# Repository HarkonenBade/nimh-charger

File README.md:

# nimh-charger
Ni-MH and Ni-Cd battery trickle charger

Based on the schematic and design of Big Clive https://www.youtube.com/watch?v=wVnAH17f4jg with my own improvements to the PCB design for two layer manufacture.

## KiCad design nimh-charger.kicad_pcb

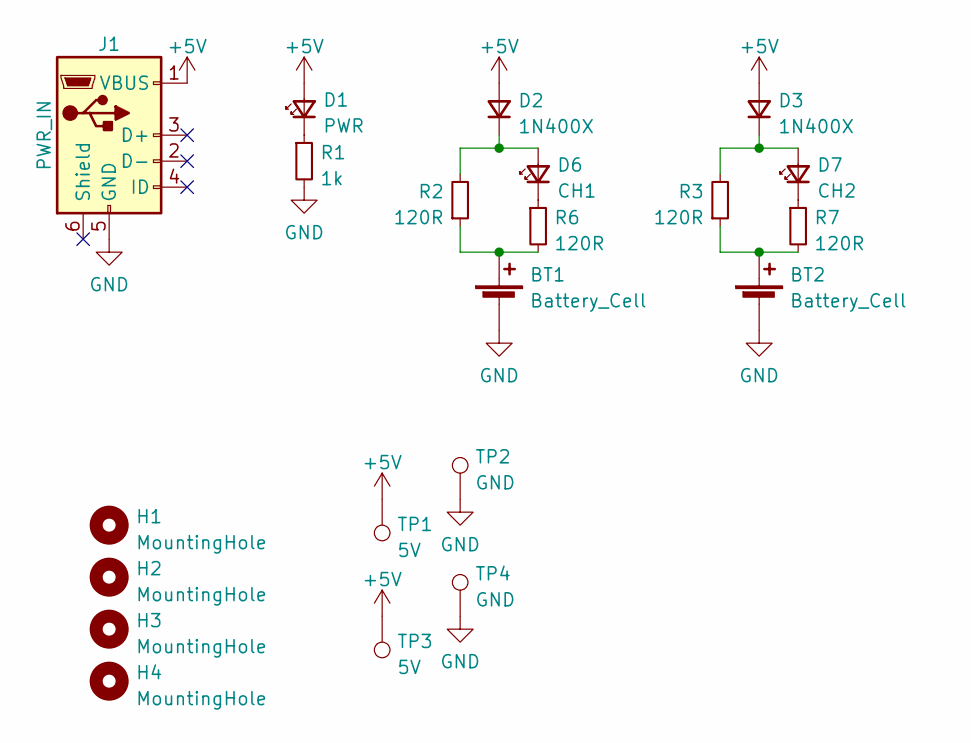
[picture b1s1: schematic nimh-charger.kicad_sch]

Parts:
BT1, BT2: Battery_Cell; BatteryHolder_Keystone_2460_1xAA
D1: PWR; LED_0805_2012Metric; LCSC C965812
D2, D3: 1N400X; D_SMA; LCSC C2892325
D6: CH1; LED_0805_2012Metric; LCSC C965812
D7: CH2; LED_0805_2012Metric; LCSC C965812
H1, H2, H3, H4: MountingHole; MountingHole_3.2mm_M3_DIN965
J1: PWR_IN; USB_Micro-B_Molex-105017-0001; LCSC C136000
R1: 1k; R_0805_2012Metric
R2, R3, R6, R7: 120R; R_0805_2012Metric
TP1, TP3: 5V; TestPoint_Pad_2.5x2.5mm
TP2, TP4: GND; TestPoint_Pad_2.5x2.5mm

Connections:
+5V: D1.2 (A), D2.2 (A), D3.2 (A), J1.1 (VBUS), TP1.1, TP3.1
GND: BT1.2 (-), BT2.2 (-), J1.5 (GND), R1.2, TP2.1, TP4.1
unnamed: BT1.1 (+), R2.1, R6.2
unnamed: D1.1 (K), R1.1
unnamed: D2.1 (K), D6.2 (A), R2.2
unnamed: D3.1 (K), D7.2 (A), R3.2
unnamed: D6.1 (K), R6.1
unnamed: D7.1 (K), R7.1
unnamed: BT2.1 (+), R3.1, R7.2

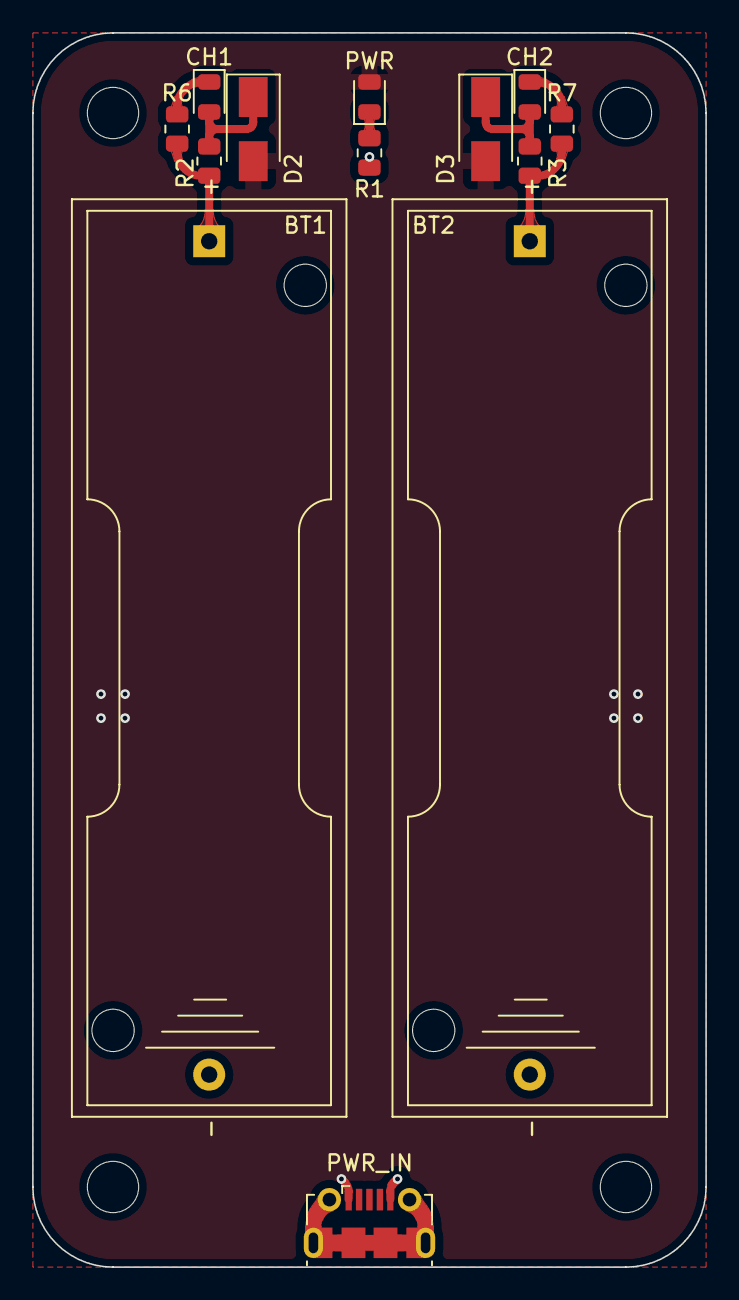
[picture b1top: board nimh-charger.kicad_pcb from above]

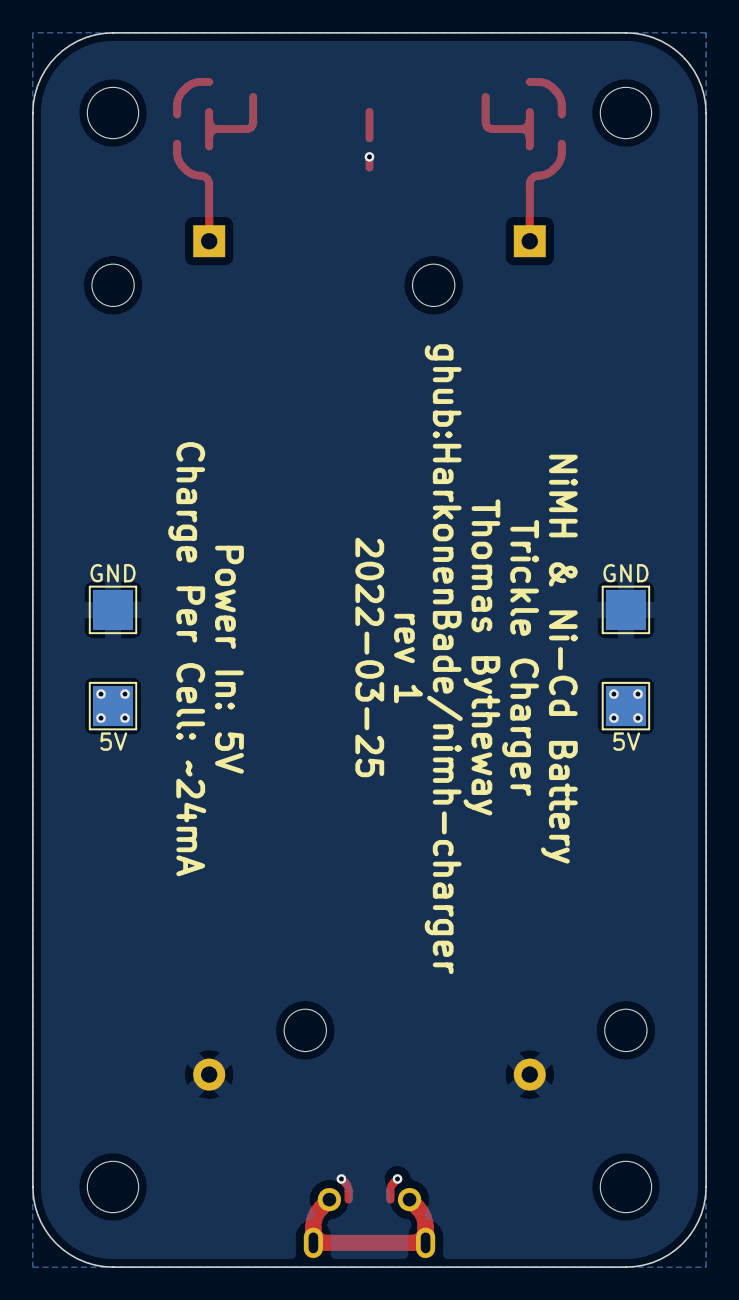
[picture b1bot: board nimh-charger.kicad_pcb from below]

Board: 2 copper layers, 42.0 x 77.0 mm, 21 parts (4 on the bottom side), 9 nets.

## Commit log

2022-03-24 Initial Design
2022-03-25 Chonkier pads on resistors for hand soldering, also wider tracks
2022-03-25 Final tweaks and silk
2022-03-25 Gerbers
2022-03-25 Added LCSC part numbers and ibom
2022-04-24 PCB Model and Case
2022-04-24 Hide Backups
2022-04-24 SMD 2-cell chaining version
2022-04-24 Meltiiing
